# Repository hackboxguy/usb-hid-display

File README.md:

# usb-hid-display

A firmware for Raspberry Pi Pico (RP2040) that turns cheap off-the-shelf components (rotary encoder, push buttons, SSD1306 OLED) into a standalone USB micro-panel for embedded Linux devices.

## What is this?

This firmware creates a USB composite device with two interfaces:

- **HID Mouse** — The rotary encoder and directional buttons appear as a standard USB mouse to the host. A host-side daemon (such as [micropanel](https://github.com/hackboxguy/micropanel/tree/opus_4_6_improvements)) interprets the relative mouse movements as menu navigation: up, down, left, right, and select.
- **CDC Serial** (`/dev/ttyACMx`) — The host writes binary commands over this serial port to control the SSD1306 OLED display: draw text, progress bars, set brightness, etc.

Together, these two interfaces form a self-contained hardware menu system — physical buttons for input, OLED for output — driven entirely from the host over a single USB cable. No drivers required; the device uses standard USB HID and CDC ACM classes supported by all major operating systems.

## Features

- USB HID Mouse: rotary encoder for horizontal movement, directional buttons for X/Y navigation, push button for left-click/select
- USB CDC Serial: binary command protocol to draw text, progress bars, control brightness/power/inversion on the SSD1306
- Single USB connection: both HID and CDC interfaces available simultaneously
- Robust I2C communication with timeouts (no hangs if display disconnects)
- Proper quadrature decoding with Gray code for reliable rotary input
- Per-button debouncing for all inputs
- Unique USB serial number derived from RP2040 chip ID
- Runtime landscape/portrait orientation via GPIO jumper (single firmware binary)

## Hardware Variants

### Custom PCB — RP2040-Micropanel

A purpose-built PCB designed in KiCad with a Waveshare RP2040-Zero module, SSD1306 OLED, and 5 tactile buttons on a compact board. KiCad project files are available in the [`hardware/`](hardware/) directory.

### Prototype — Hand-Soldered

The same firmware runs on any RP2040 board with hand-wired connections on a general-purpose PCB. No custom PCB required — see the wiring diagram in the [Directional Push Buttons](#directional-push-buttons-active-low-directly-connected-to-gnd) section below.

## Hardware Requirements

- Raspberry Pi Pico (RP2040)
- SSD1306 OLED display (128x64, I2C version)
- Rotary encoder with push button
- 4x directional push buttons (active-low, directly connected to GPIO with internal pull-ups)
- Micro USB cable
- Optional: jumper wire for portrait mode (GPIO 27 to GND)

## Hardware Connections

### SSD1306 OLED Display (I2C)

| Signal | GPIO | Pico Pin |
|--------|------|----------|
| SDA    | GPIO 4 | Pin 6 |
| SCL    | GPIO 5 | Pin 7 |
| VCC    | 3.3V | Pin 36 |
| GND    | GND  | Pin 38 |

### Rotary Encoder

| Signal     | GPIO    | Pico Pin |
|------------|---------|----------|
| CLK (A)    | GPIO 10 | Pin 14   |
| DT (B)     | GPIO 11 | Pin 15   |
| SW (Button)| GPIO 12 | Pin 16   |
| VCC        | 3.3V    | Pin 36   |
| GND        | GND     | Pin 38   |

### Orientation Jumper

The firmware detects landscape or portrait mode at boot from GPIO 27:

| GPIO 27 State | Orientation |
|---------------|-------------|
| Floating (internal pull-up → HIGH) | **Landscape** (default) |
| Connected to GND (LOW) | **Portrait** |

No separate firmware builds needed — a single `.uf2` handles both orientations. The detected orientation is reflected in the USB product string (`"USB HID Display (landscape)"` or `"USB HID Display (portrait)"`).

### Directional Push Buttons (active-low, directly connected to GND)

Pre-compiled `.uf2` binary with this GPIO config can be downloaded from [here](https://github.com/hackboxguy/usb-hid-display/blob/main/rp2040/bin/usb_hid_display.uf2?raw=true).

The table below shows the **landscape orientation** (default) mapping. In portrait mode, the physical button roles rotate: LEFT becomes UP, RIGHT becomes DOWN, DOWN becomes LEFT, UP becomes RIGHT.

| Button (Landscape) | GPIO    | HID Action     |
|---------------------|---------|----------------|
| LEFT   | GPIO 7  | Mouse X = -5   |
| RIGHT  | GPIO 6  | Mouse X = +5   |
| UP     | GPIO 8  | Mouse Y = -5   |
| DOWN   | GPIO 15 | Mouse Y = +5   |
| ENTER  | GPIO 14 | Mouse Left Click (shared with rotary SW) |

Portrait/landscape mapping summary:

| Physical Button | Landscape Action | Portrait Action |
|-----------------|------------------|-----------------|
| LEFT (GPIO 7)   | Left             | Up              |
| RIGHT (GPIO 6)  | Right            | Down            |
| UP (GPIO 8)     | Up               | Right           |
| DOWN (GPIO 15)  | Down             | Left            |
| ENTER (GPIO 14) | Select (BTN_LEFT)| Select (BTN_LEFT) |

**Note:** Each directional button press generates two HID movement events (one immediate, one after ~16ms) to match rotary encoder step responsiveness. Host-side daemons should account for this when interpreting navigation input.

## Serial Command Protocol

The device exposes a CDC serial port (`/dev/ttyACMx`) that accepts binary commands to control the display:

| Command | Code | Format | Description |
|---------|------|--------|-------------|
| Clear   | `0x01` | `[0x01]` | Clear entire display |
| Draw Text | `0x02` | `[0x02][x][y][len][text...]` | Draw `len` bytes of text at pixel position (x, y). Max len=124. Text Y is 8-pixel aligned (page-based): use multiples of 8 (0, 8, 16, 24, 32, 40, 48, 56) |
| Set Cursor | `0x03` | `[0x03][x][y]` | Set cursor to pixel position (x, y) |
| Invert  | `0x04` | `[0x04][0/1]` | Normal or inverted display mode |
| Brightness | `0x05` | `[0x05][0-255]` | Set display contrast/brightness |
| Progress Bar | `0x06` | `[0x06][x][y][w][h][0-100]` | Draw progress bar at (x, y) with width, height, and percentage |
| Power   | `0x07` | `[0x07][0/1]` | Turn display off or on |

### Protocol Limits and Caveats

- `MAX_CMD_SIZE` is 128 bytes total per command buffer.
- Commands that exceed the buffer are truncated to avoid parser desynchronization.
- `CMD_DRAW_TEXT` uses length-based framing: the `len` byte specifies exactly how many text bytes follow (max 124).
- All commands have deterministic framing — fixed-length (0x01, 0x03-0x07) or length-prefixed (0x02).
- Text Y is page-based (8-pixel rows): use `0, 8, 16, ..., 56`.

### Example (Python)

```python
import serial

ser = serial.Serial('/dev/ttyACM0', timeout=1)

# Clear display
ser.write(bytes([0x01]))

# Draw text "Hello" at position (0, 0) — len=5
ser.write(bytes([0x02, 0, 0, 5]) + b'Hello')

# Draw progress bar at (10, 30), 108px wide, 12px tall, 75%
ser.write(bytes([0x06, 10, 30, 108, 12, 75]))

# Set brightness to max
ser.write(bytes([0x05, 255]))
```

## Test Commands (optional, build-time enabled)

When built with `-DENABLE_TEST_COMMANDS=ON`, the firmware accepts command `0xF0` for automated hardware testing. This allows the host test framework to inject simulated HID input events through the CDC serial port without physically pressing buttons.

Production firmware ignores `0xF0` entirely.

| Subcommand | Code | Action | HID Output |
|------------|------|--------|------------|
| Ping | `[0xF0][0x00]` | Replies `[0xF0][0x00]` via CDC | None |
| Rotate CW | `[0xF0][0x01]` | One clockwise encoder step | REL_X = -5 |
| Rotate CCW | `[0xF0][0x02]` | One counter-clockwise step | REL_X = +5 |
| Button press | `[0xF0][0x03]` | Encoder push (press + release) | BTN_LEFT down, then up after ~50ms |
| Navigate up | `[0xF0][0x04]` | Simulated UP button | 2x REL_Y = -5 (~16ms apart) |
| Navigate down | `[0xF0][0x05]` | Simulated DOWN button | 2x REL_Y = +5 (~16ms apart) |
| Navigate left | `[0xF0][0x06]` | Simulated LEFT button | 2x REL_X = -5 (~16ms apart) |
| Navigate right | `[0xF0][0x07]` | Simulated RIGHT button | 2x REL_X = +5 (~16ms apart) |

Navigation test commands produce orientation-independent logical directions — the same HID output regardless of landscape/portrait build.

**Timing:** Allow at least 60ms between nav commands and 80ms after button press before sending the next test command. The host test framework can detect test firmware by sending ping and waiting 500ms for a reply.

## Building the Firmware

### Prerequisites

```bash
sudo apt update
sudo apt install git cmake gcc-arm-none-eabi libnewlib-arm-none-eabi build-essential libstdc++-arm-none-eabi-newlib
```

### Clone and build

```bash
git clone --recursive https://github.com/raspberrypi/pico-sdk.git ~/pico-sdk
export PICO_SDK_PATH=~/pico-sdk

git clone https://github.com/hackboxguy/usb-hid-display.git
cd usb-hid-display/rp2040/
mkdir build && cd build
cmake .. -DFIRMWARE_VERSION=1.0.0
make -j$(nproc)
```

#### Build options

| Option | Default | Description |
|--------|---------|-------------|
| `FIRMWARE_VERSION` | `0.0.0` | Firmware version in `X.Y.Z` format (each digit 0-9) |
| `ENABLE_TEST_COMMANDS` | `OFF` | Enable test/debug commands (`0xF0`) for automated testing |

`FIRMWARE_VERSION` is embedded in USB descriptors and exposed to the host via sysfs during USB enumeration. Orientation is detected at runtime from the GPIO 27 jumper (no build flag needed).

#### Test command build

To build firmware with test commands enabled (for automated hardware testing):

```bash
cmake .. -DENABLE_TEST_COMMANDS=ON -DFIRMWARE_VERSION=1.0.1
make -j$(nproc)
```

Production builds (without `-DENABLE_TEST_COMMANDS=ON`) ignore the test command byte entirely.

### Flashing

1. Hold the **BOOTSEL** button on the Pico and connect it via USB
2. The Pico mounts as a USB mass storage device
3. Copy the firmware:

```bash
# Check dmesg for the device node (e.g. /dev/sda1)
sudo mount /dev/sdXN /mnt
sudo cp usb_hid_display.uf2 /mnt/
sudo umount /mnt
```

After flashing, the device enumerates as:
- `/dev/input/eventX` -- HID mouse (rotary encoder + buttons)
- `/dev/ttyACMX` -- CDC serial port (display commands)

### Verify

```bash
# Test HID input events
sudo evtest /dev/input/eventX

# Test display commands
echo -ne '\x01' > /dev/ttyACM0          # clear display
echo -ne '\x02\x00\x00\x05Hello' > /dev/ttyACM0  # draw "Hello" at (0,0), len=5
```

## USB Device Info

| Field | Value |
|-------|-------|
| Vendor ID  | `0x1209` (pid.codes) |
| Product ID | `0x0001` |
| Manufacturer | hackboxguy |
| Product | `USB HID Display (<orientation>)` — reflects runtime GPIO jumper state |
| Serial | Unique per chip (from RP2040 flash ID) |
| bcdDevice | Firmware version as BCD (e.g. `0x1010` for v1.0.1) |

### Version Encoding

`FIRMWARE_VERSION=X.Y.Z` is encoded as USB `bcdDevice = 0xXYZ0`:

| Version | bcdDevice |
|---------|-----------|
| `1.0.0` | `1000`    |
| `1.0.1` | `1010`    |
| `1.1.0` | `1100`    |

### Reading firmware info from host

The daemon (or any tool) can read firmware version and orientation from sysfs without opening the serial port:

```bash
# Find the device (filter by VID:PID)
DEVPATH=$(grep -rl "1209" /sys/bus/usb/devices/*/idVendor 2>/dev/null | head -1 | xargs dirname)

# Read product string (includes orientation)
cat "$DEVPATH/product"    # e.g. "USB HID Display (portrait)"

# Read firmware version (BCD format)
cat "$DEVPATH/bcdDevice"  # e.g. "1100" for v1.1.0
```

## Host Integration

Use stable paths instead of raw `eventX` / `ttyACM0` indices:

```bash
# serial path
ls -l /dev/serial/by-id/

# input path
ls -l /dev/input/by-id/
```

Optional udev rule for a stable symlink:

```bash
# /etc/udev/rules.d/99-usb-hid-display.rules
SUBSYSTEM=="tty", ATTRS{idVendor}=="1209", ATTRS{idProduct}=="0001", SYMLINK+="usb-hid-display-%s{serial}"
```

```bash
sudo udevadm control --reload-rules
sudo udevadm trigger
```

## Troubleshooting

| Symptom | Likely Cause | Check / Fix |
|---------|--------------|-------------|
| No `/dev/ttyACM*` | USB cable or enumeration issue | Try a data-capable cable, check `dmesg -w` |
| No HID events | Wrong `eventX` selected | Use `evtest` and pick matching device from `/dev/input/by-id` |
| Display stays blank | I2C wiring/power/address issue | Verify SDA/SCL pins, 3.3V power, GND, SSD1306 address `0x3C` |
| Buttons feel double-step | Intended dual-event behavior | Account for two events per press in daemon logic |
| Wrong navigation direction | Orientation mismatch | Check GPIO 27 jumper: GND = portrait, floating = landscape |
| Permission denied on device files | User/group access | Add user to `dialout` and `input` groups or use udev permissions |

## License

See [LICENSE](LICENSE) for details.

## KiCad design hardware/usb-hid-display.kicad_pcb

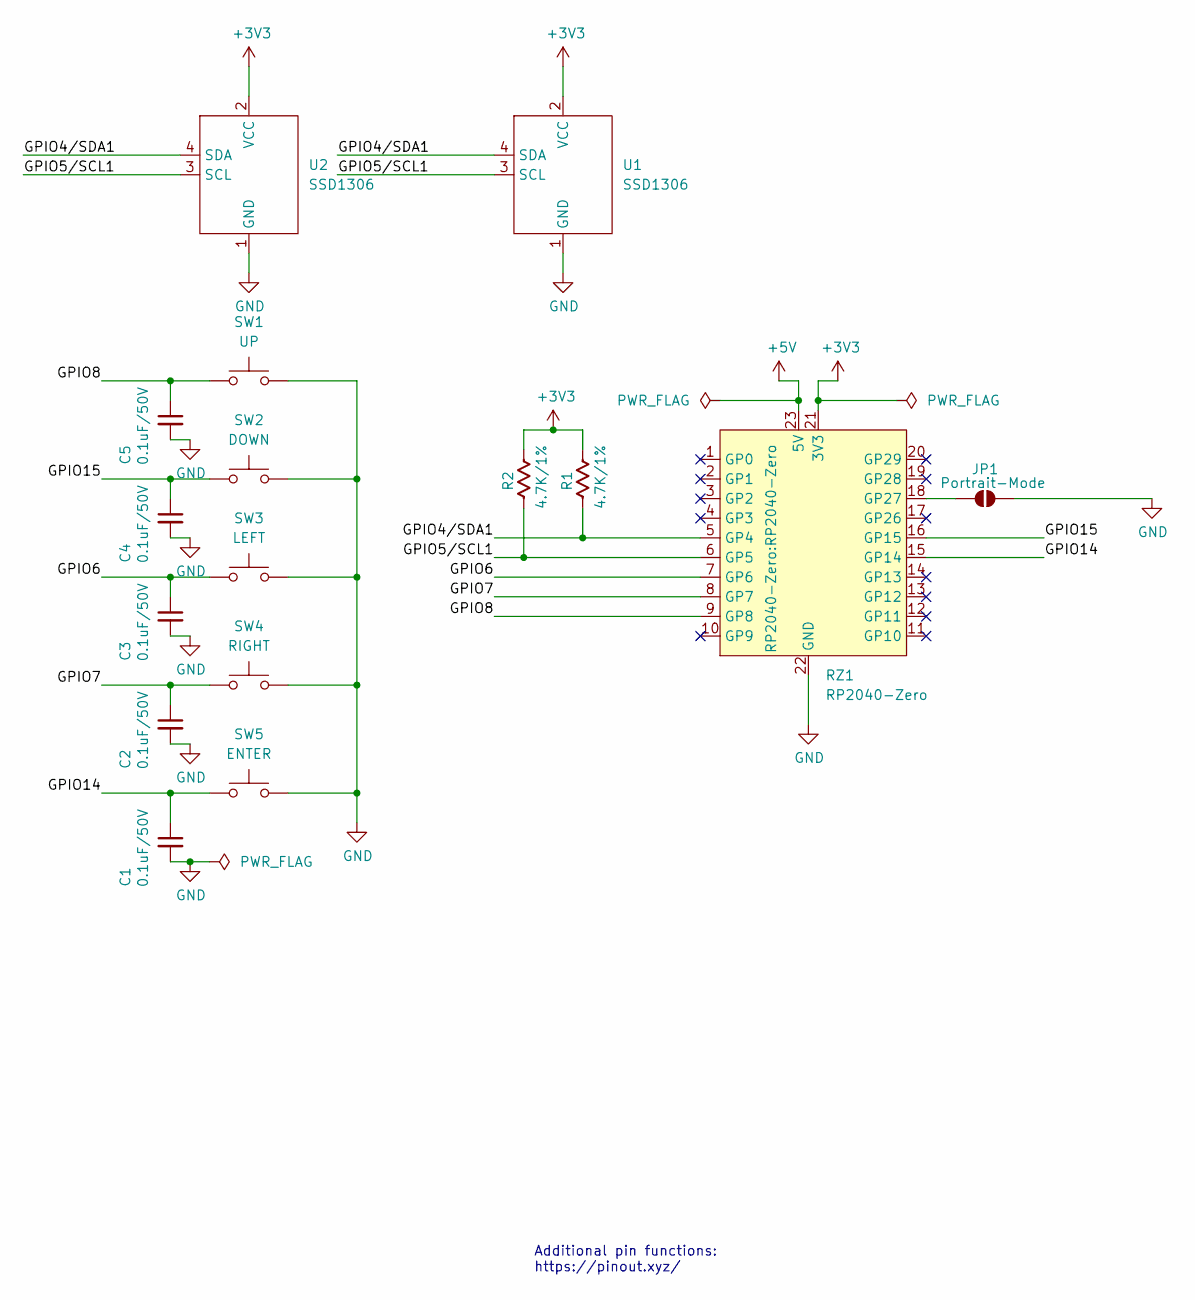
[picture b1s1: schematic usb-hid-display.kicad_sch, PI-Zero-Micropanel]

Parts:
C1, C2, C3, C4, C5: 0.1uF/50V; C_0805_2012Metric
JP1: Portrait-Mode; SolderJumper-2_P1.3mm_Open_TrianglePad1.0x1.5mm
R1, R2: 4.7K/1%; R_0805_2012Metric
RZ1: RP2040-Zero
SW1: UP; SW_PUSH_6mm
SW2: DOWN; SW_PUSH_6mm
SW3: LEFT; SW_PUSH_6mm
SW4: RIGHT; SW_PUSH_6mm
SW5: ENTER; SW_PUSH_6mm
U1, U2: SSD1306; ssd1306-module

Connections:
+3V3: R1.2, R2.2, RZ1.21 (3V3), U1.2 (VCC), U2.2 (VCC)
+5V: RZ1.23 (5V)
/GPIO4/SDA1: R1.1, RZ1.5 (GP4), U1.4 (SDA), U2.4 (SDA)
/GPIO5/SCL1: R2.1, RZ1.6 (GP5), U1.3 (SCL), U2.3 (SCL)
/GPIO6: C3.1, RZ1.7 (GP6), SW3.1
/GPIO7: C2.1, RZ1.8 (GP7), SW4.1
/GPIO8: C5.1, RZ1.9 (GP8), SW1.1
/GPIO14: C1.1, RZ1.15 (GP14), SW5.1
/GPIO15: C4.1, RZ1.16 (GP15), SW2.1
GND: C1.2, C2.2, C3.2, C4.2, C5.2, JP1.2 (B), RZ1.22 (GND), SW1.2, SW2.2, SW3.2, SW4.2, SW5.2, U1.1 (GND), U2.1 (GND)
unnamed: JP1.1 (A), RZ1.18 (GP27)

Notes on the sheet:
Additional pin functions: https://pinout.xyz/

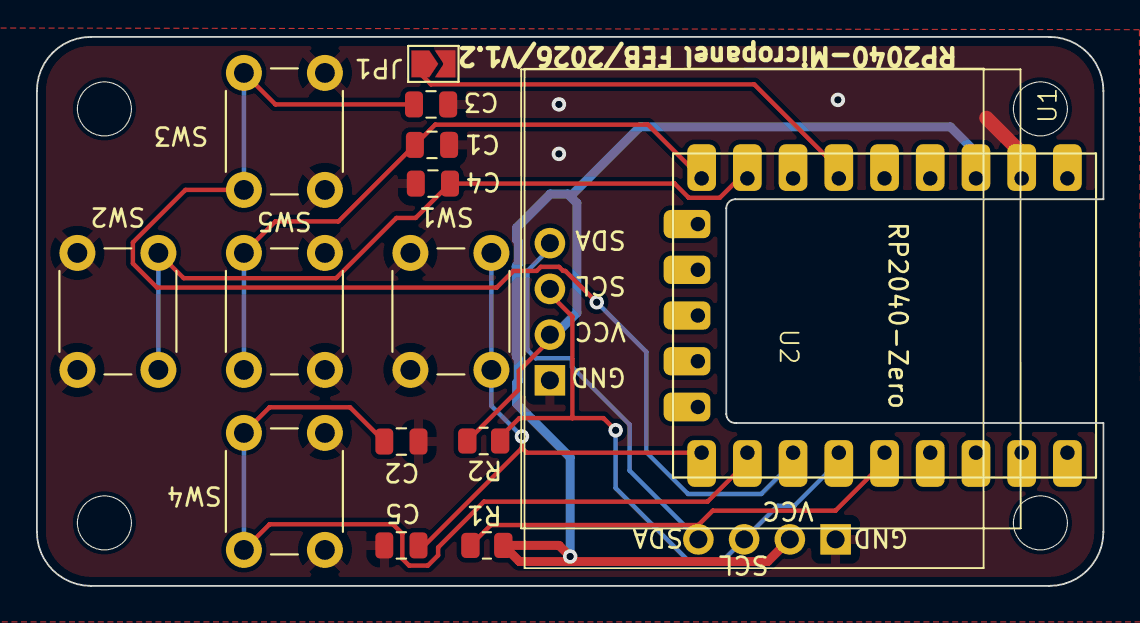
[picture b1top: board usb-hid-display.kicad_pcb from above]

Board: 2 copper layers, 59.2 x 30.5 mm, 20 parts (0 on the bottom side), 10 nets.

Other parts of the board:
MH1, MH2, MH3, MH4: MountingHole_2.7mm_M2.5

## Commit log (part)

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2025-04-16 added first working version of usb-composite-device fmw for rp2040
2025-04-16 updated README.md file with build instructions
2025-04-16 reversed KEY_REL value for clock-wise and counter-clockwise direction of rotary encoder
2025-04-18 added ssd1306 power on/off command
2025-04-18 fixed missing 16th char in a line
2025-04-25 added sensing up/down/left/right directional pushbuttons for REL_X/REL_Y mouse events
2025-04-25 updated README.md for directional push button support
2025-04-25 updated binary as per latest directional push-button support
2025-04-30 changed directional button gpio for easy soldering of io pins for rp2040 usb dongle
2025-05-18 added photos to readme.md
2025-05-30 updated readme.md with buttons-wiring.jpg picture
2025-05-30 updated readme and code and picture as per updated gpio config for directional push buttons
2025-05-30 updated readme with firmware download link
2026-02-07 changed the top-bottom buttons for landscape orientation
2026-02-24 fixed micropanel's href
